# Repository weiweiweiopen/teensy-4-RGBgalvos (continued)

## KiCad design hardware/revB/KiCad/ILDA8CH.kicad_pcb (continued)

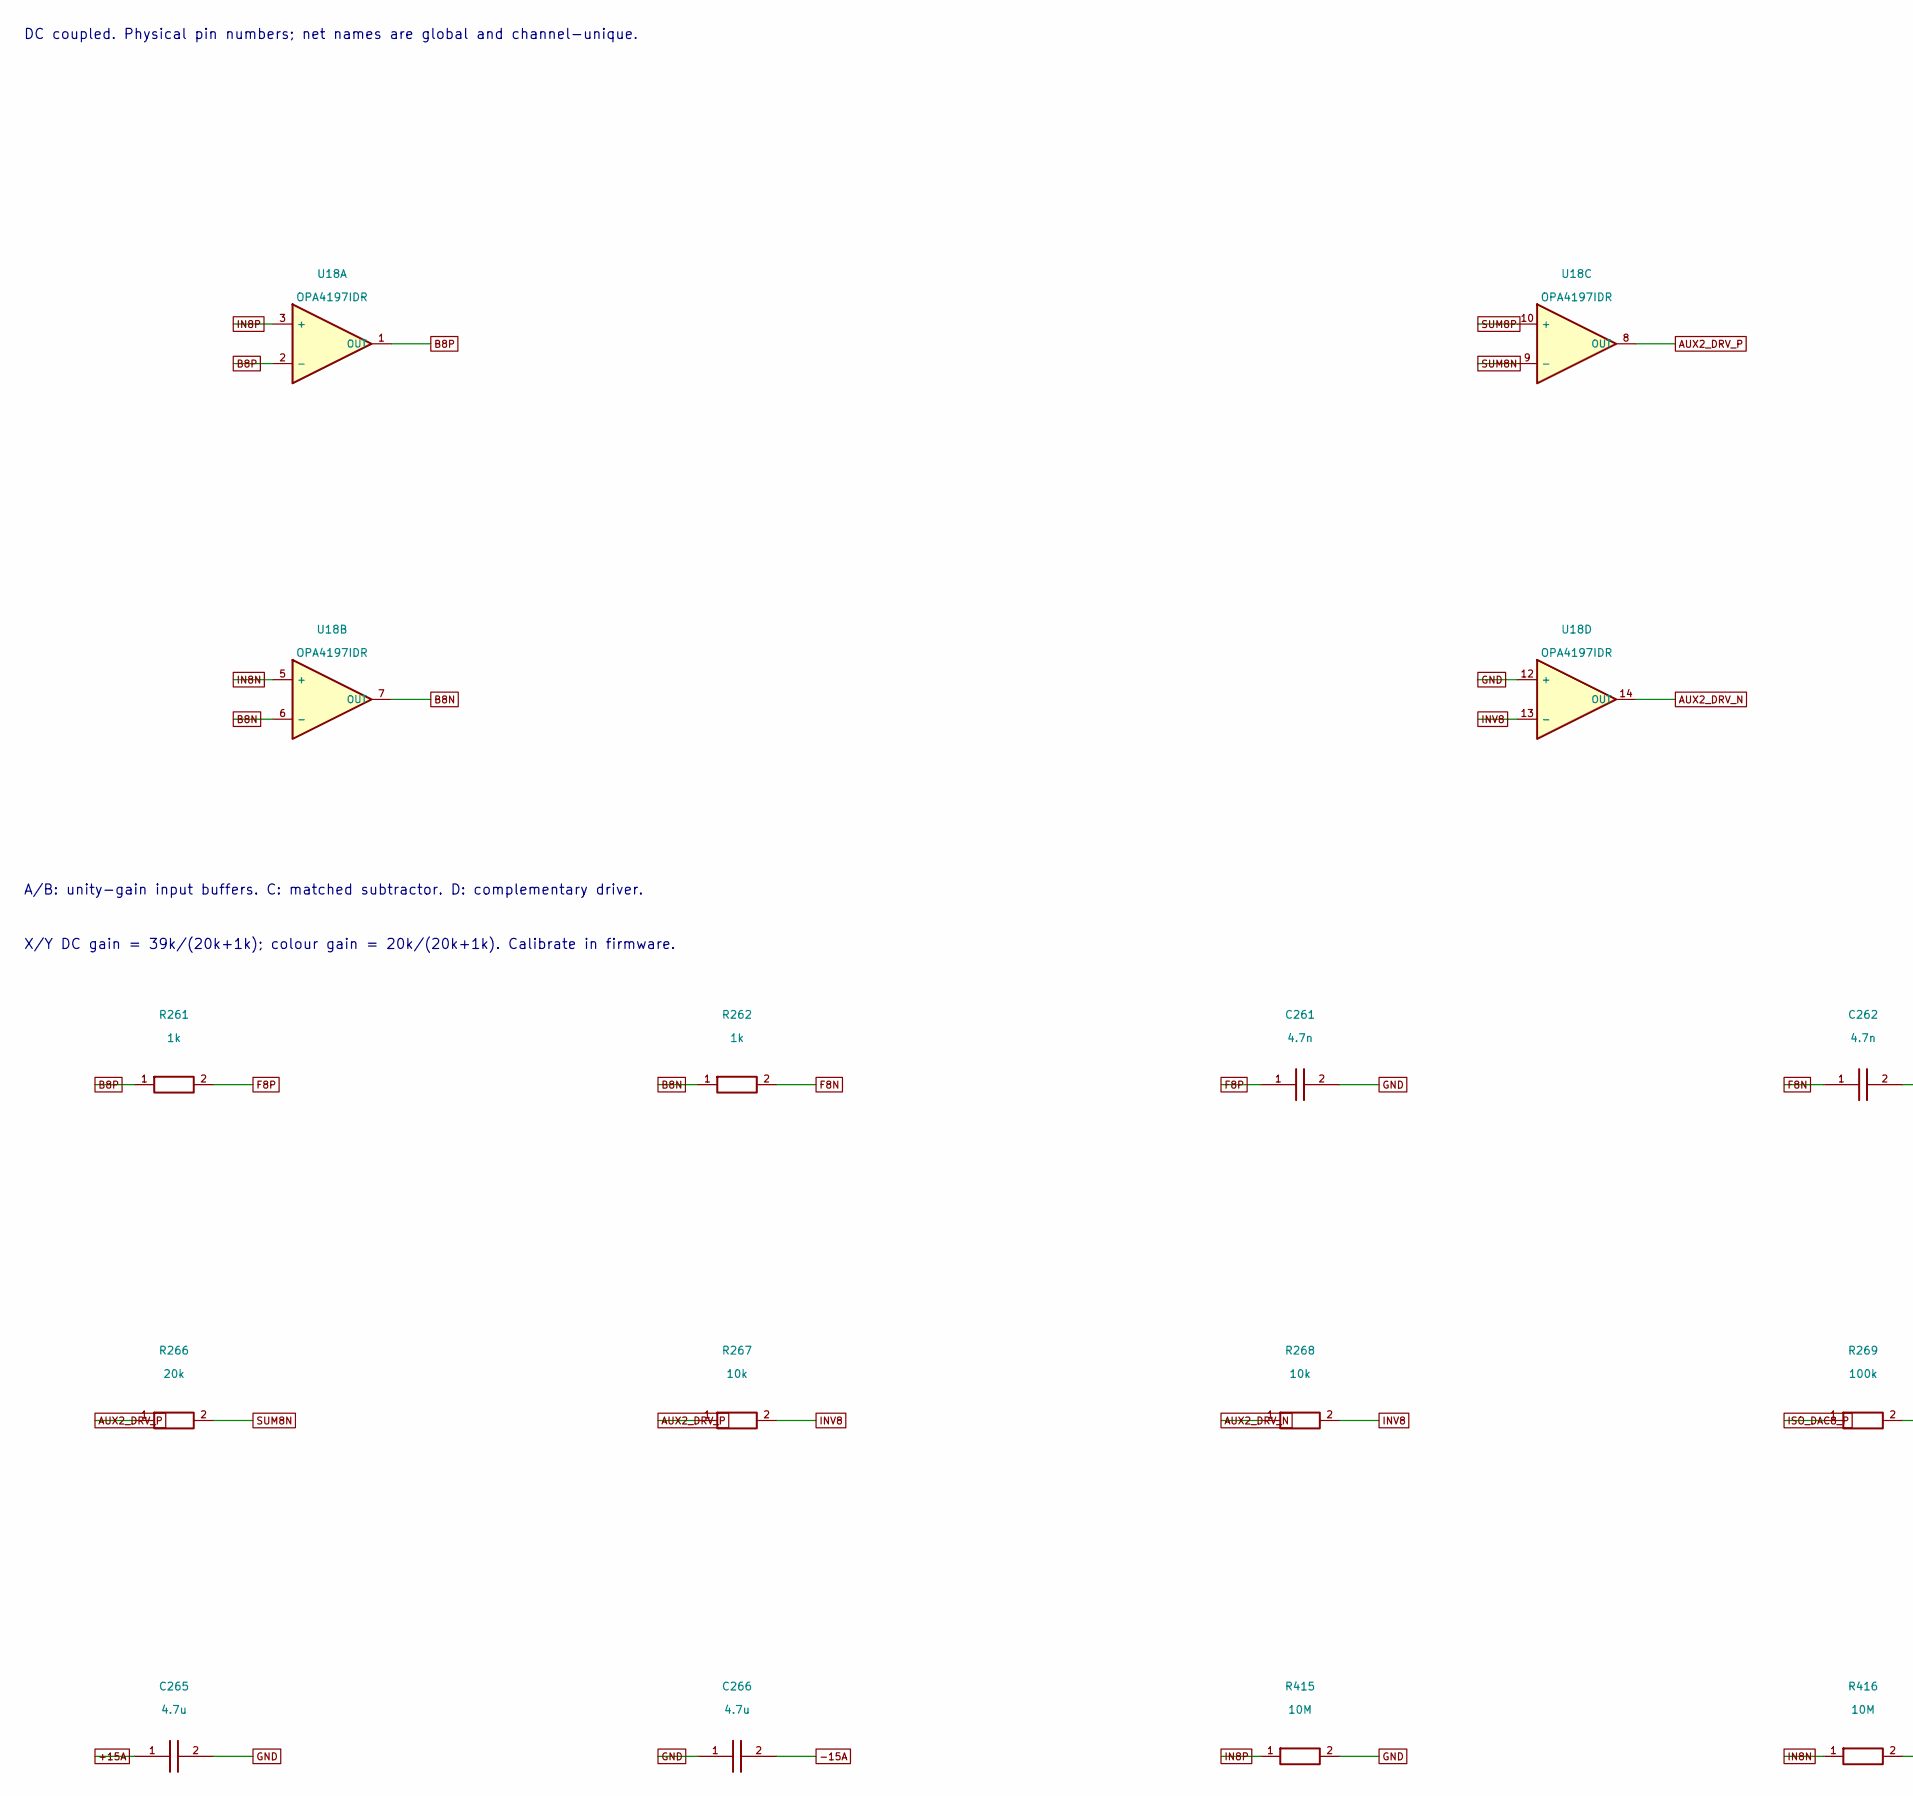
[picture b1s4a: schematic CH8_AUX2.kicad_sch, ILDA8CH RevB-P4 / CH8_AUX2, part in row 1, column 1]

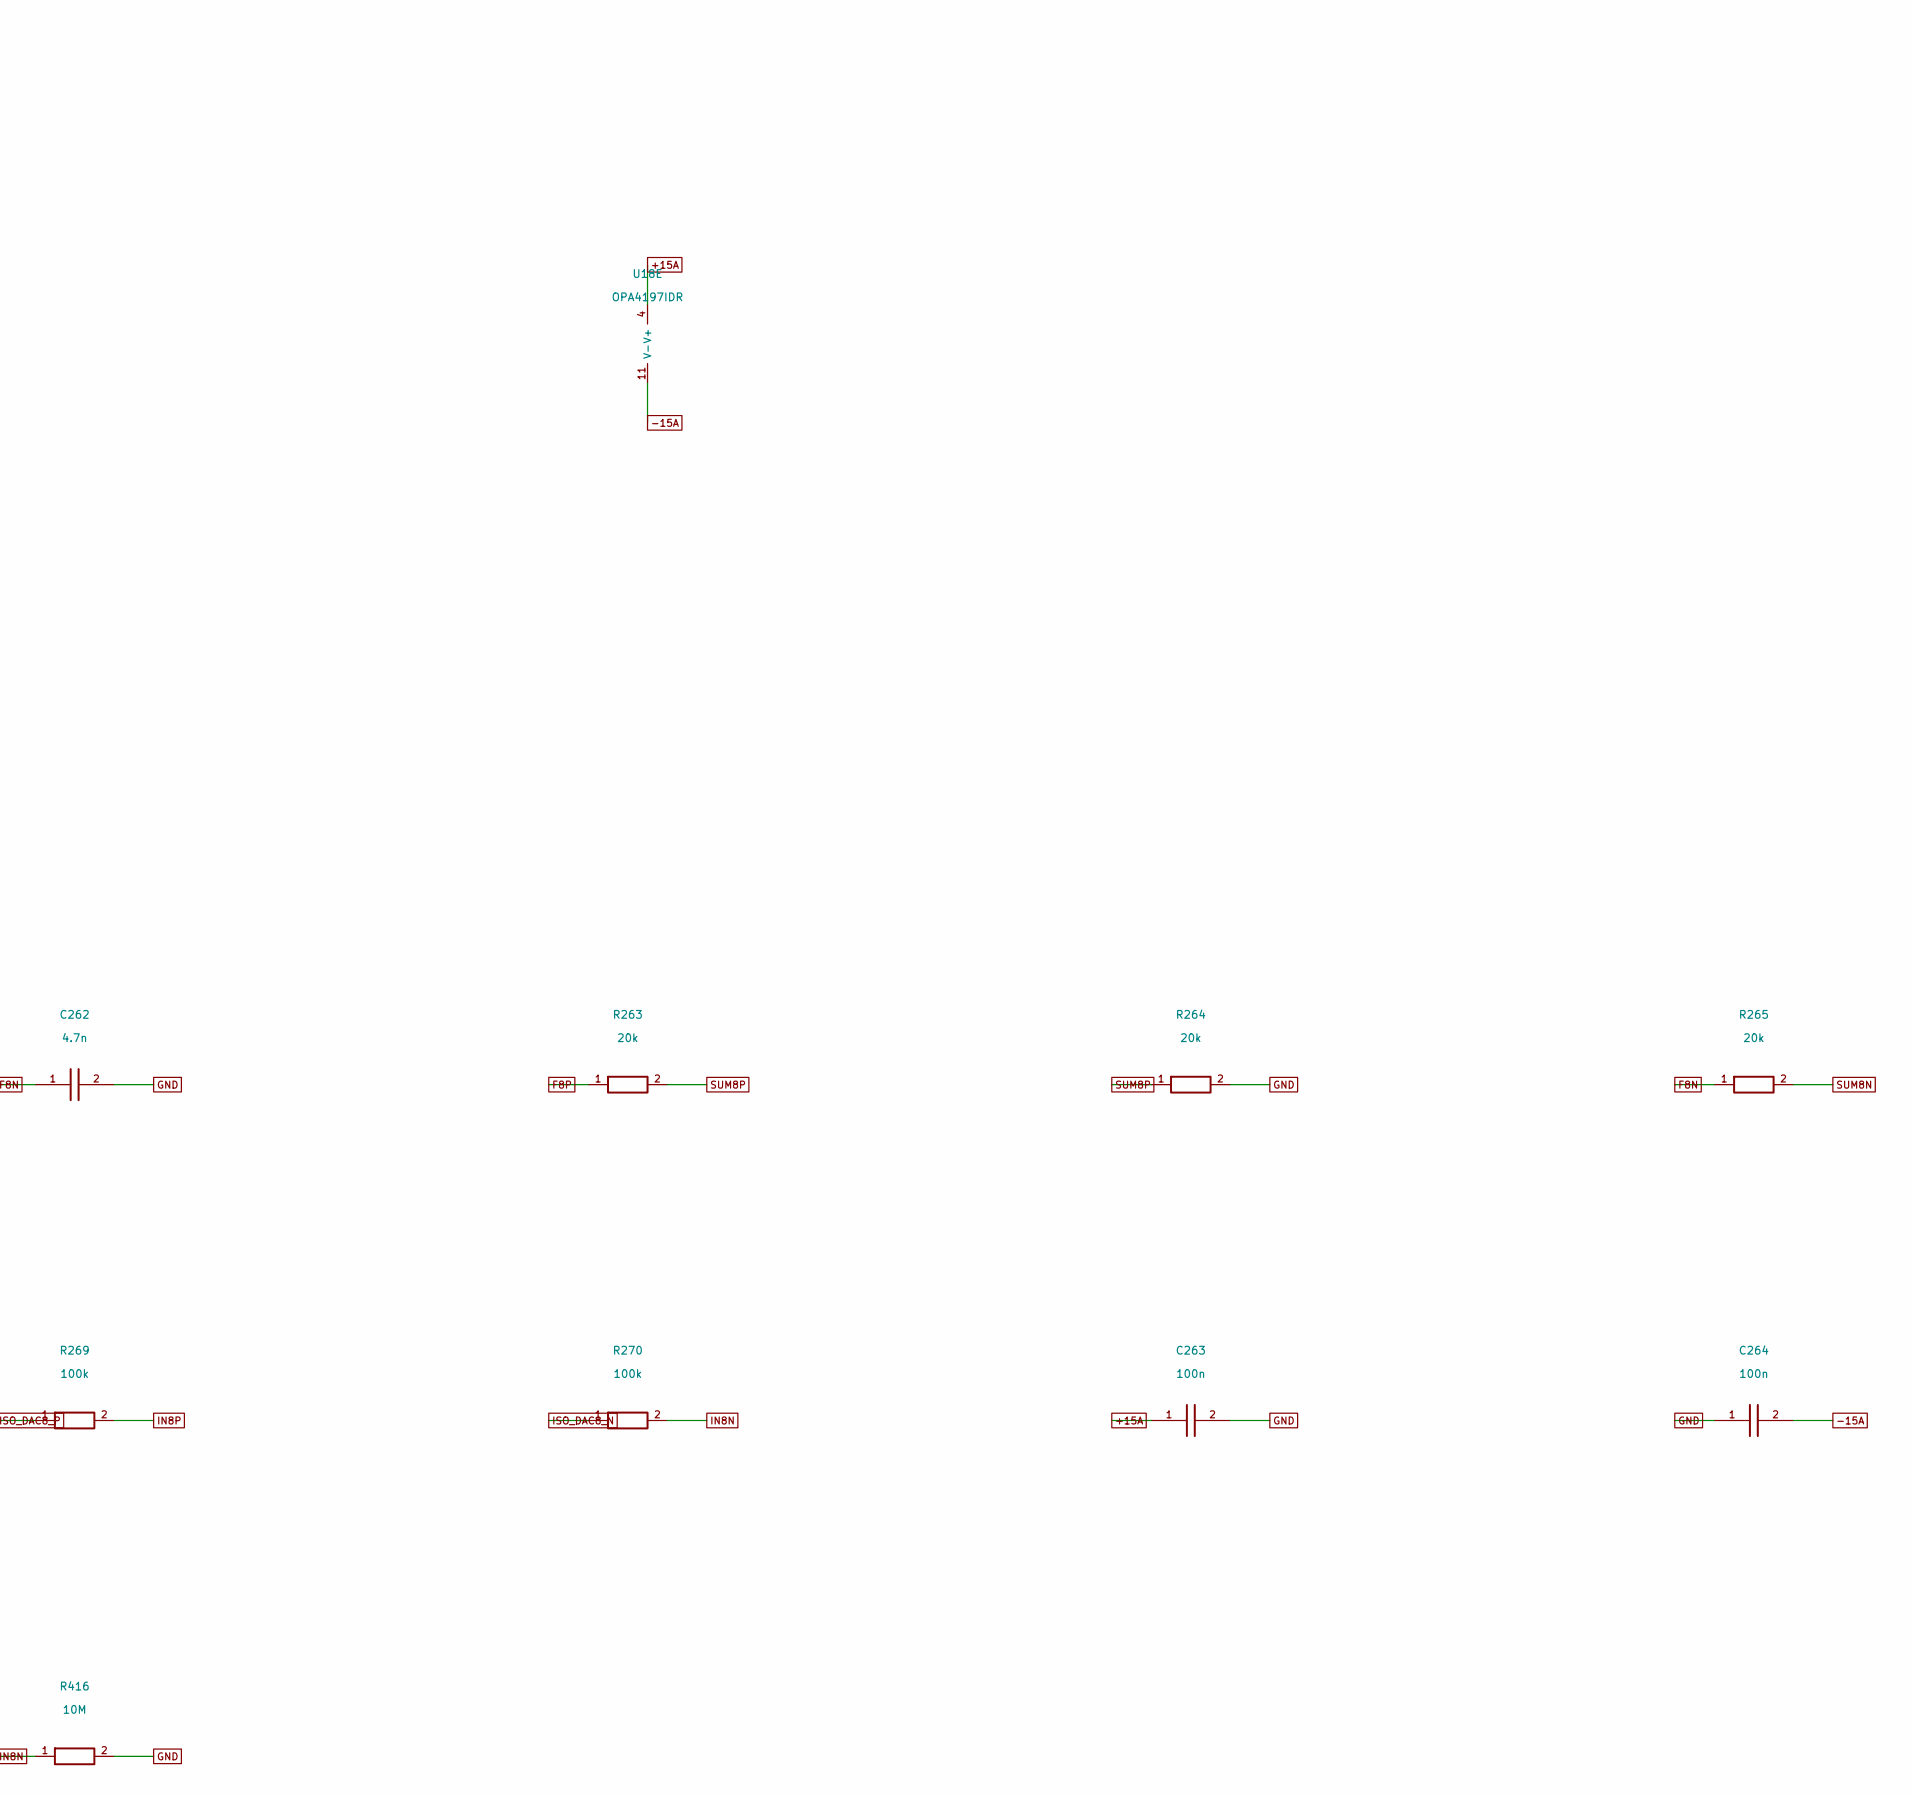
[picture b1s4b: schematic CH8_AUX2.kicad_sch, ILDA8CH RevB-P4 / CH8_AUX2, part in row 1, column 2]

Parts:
C261, C262: 4.7n; Capacitor_SMD__C_0603_1608Metric; MPN GRM1885C1H472JA01D; LCSC C85980
C263, C264: 100n; Capacitor_SMD__C_0603_1608Metric; MPN GRM188R71H104KA93D; LCSC C77055
C265, C266: 4.7u; Capacitor_SMD__C_0805_2012Metric; MPN GRM21BR61E475KA12L; LCSC C77077
R261, R262: 1k; Resistor_SMD__R_0603_1608Metric; MPN RT0603BRD071KL; LCSC C110776
R263, R264, R265, R266: 20k; Resistor_SMD__R_0603_1608Metric; MPN RT0603BRD0720KL; LCSC C723637
R267, R268: 10k; Resistor_SMD__R_0603_1608Metric; MPN RT0603BRD0710KL; LCSC C95204
R269, R270: 100k; Resistor_SMD__R_0603_1608Metric; MPN RC0603FR-07100KL; LCSC C14675
R415, R416: 10M; Resistor_SMD__R_0603_1608Metric; MPN RC0603FR-0710ML; LCSC C114606
U18: OPA4197IDR; Package_SO__SOIC-14_3.9x8.7mm_P1.27mm; MPN OPA4197IDR; LCSC C2058532

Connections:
+15A: C263.1, C265.1, U18.4 (V+); also elsewhere on the board
-15A: C264.2, C266.2, U18.11 (V-); also elsewhere on the board
AUX2_DRV_N: R268.1, U18.14 (OUT); also elsewhere on the board
AUX2_DRV_P: R266.1, R267.1, U18.8 (OUT); also elsewhere on the board
B8N: R262.1, U18.6 (-), U18.7 (OUT)
B8P: R261.1, U18.1 (OUT), U18.2 (-)
F8N: C262.1, R262.2, R265.1
F8P: C261.1, R261.2, R263.1
GND: C261.2, C262.2, C263.2, C264.1, C265.2, C266.1, R264.2, R415.2, R416.2, U18.12 (+); also elsewhere on the board
IN8N: R270.2, R416.1, U18.5 (+)
IN8P: R269.2, R415.1, U18.3 (+)
INV8: R267.2, R268.2, U18.13 (-)
ISO_DAC8_N: R270.1; also elsewhere on the board
ISO_DAC8_P: R269.1; also elsewhere on the board
SUM8N: R265.2, R266.2, U18.9 (-)
SUM8P: R263.2, R264.1, U18.10 (+)

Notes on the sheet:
DC coupled. Physical pin numbers; net names are global and channel-unique.
X/Y DC gain = 39k/(20k+1k); colour gain = 20k/(20k+1k). Calibrate in firmware.
A/B: unity-gain input buffers. C: matched subtractor. D: complementary driver.

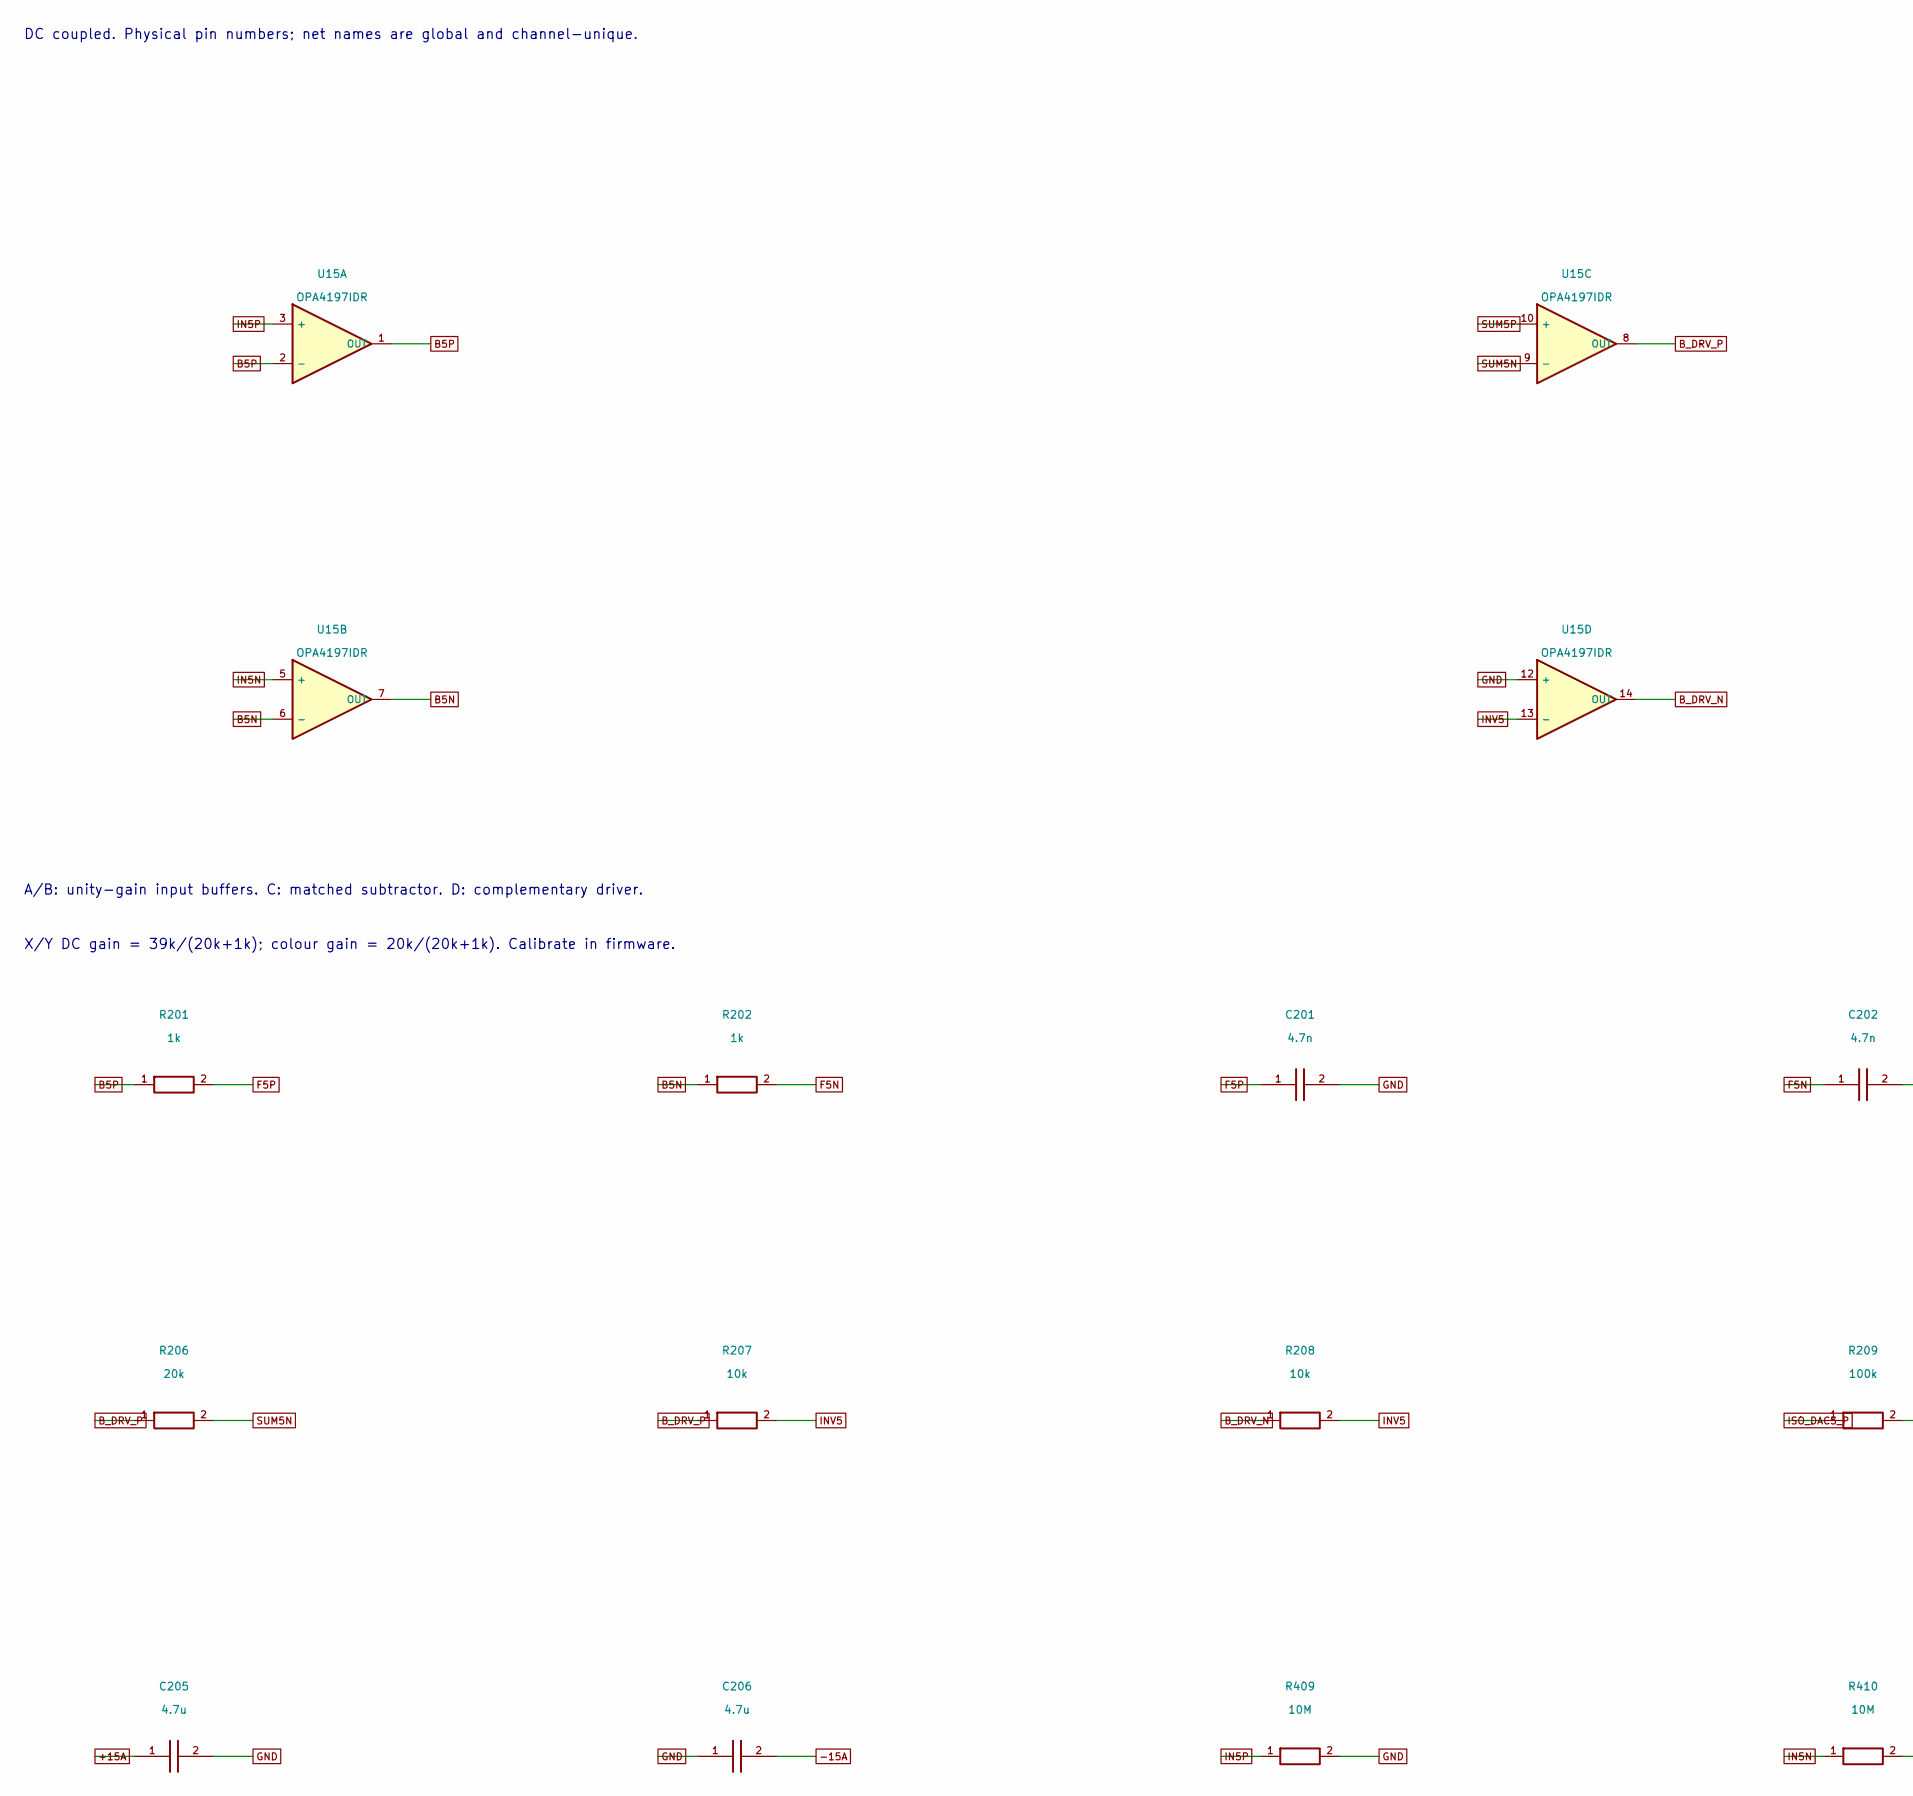
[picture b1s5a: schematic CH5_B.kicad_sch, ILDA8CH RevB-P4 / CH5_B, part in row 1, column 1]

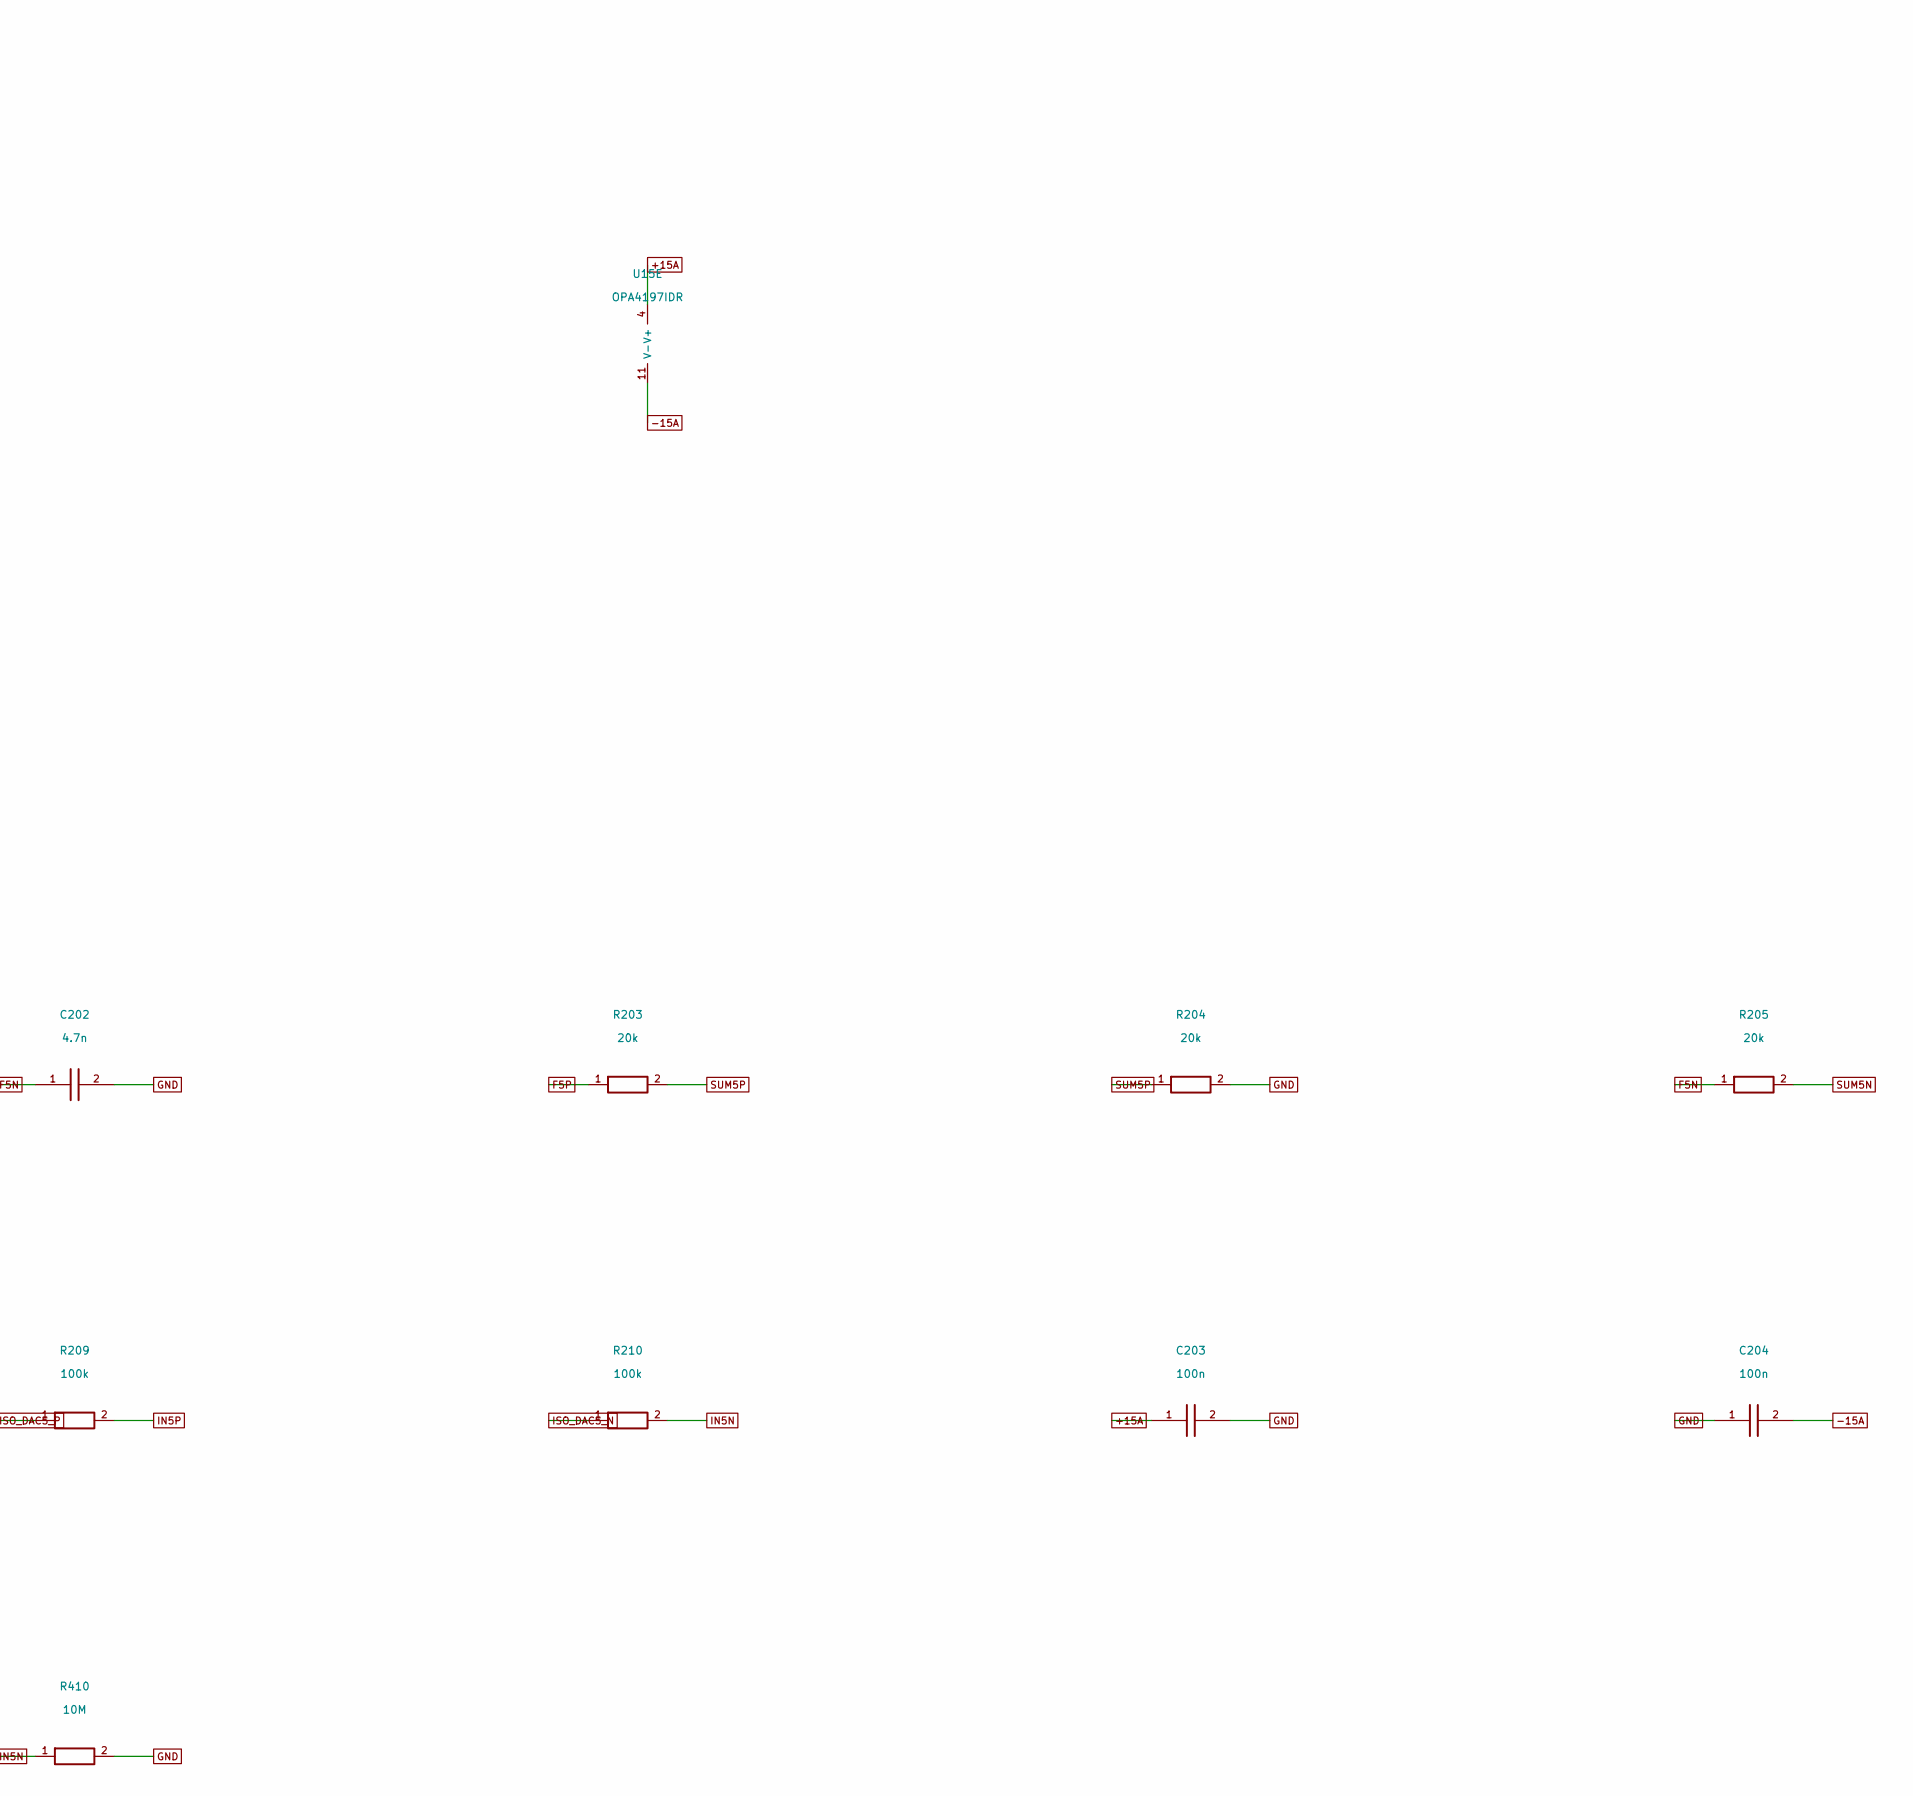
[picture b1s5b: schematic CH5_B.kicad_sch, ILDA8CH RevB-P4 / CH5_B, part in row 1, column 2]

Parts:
C201, C202: 4.7n; Capacitor_SMD__C_0603_1608Metric; MPN GRM1885C1H472JA01D; LCSC C85980
C203, C204: 100n; Capacitor_SMD__C_0603_1608Metric; MPN GRM188R71H104KA93D; LCSC C77055
C205, C206: 4.7u; Capacitor_SMD__C_0805_2012Metric; MPN GRM21BR61E475KA12L; LCSC C77077
R201, R202: 1k; Resistor_SMD__R_0603_1608Metric; MPN RT0603BRD071KL; LCSC C110776
R203, R204, R205, R206: 20k; Resistor_SMD__R_0603_1608Metric; MPN RT0603BRD0720KL; LCSC C723637
R207, R208: 10k; Resistor_SMD__R_0603_1608Metric; MPN RT0603BRD0710KL; LCSC C95204
R209, R210: 100k; Resistor_SMD__R_0603_1608Metric; MPN RC0603FR-07100KL; LCSC C14675
R409, R410: 10M; Resistor_SMD__R_0603_1608Metric; MPN RC0603FR-0710ML; LCSC C114606
U15: OPA4197IDR; Package_SO__SOIC-14_3.9x8.7mm_P1.27mm; MPN OPA4197IDR; LCSC C2058532

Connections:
+15A: C203.1, C205.1, U15.4 (V+); also elsewhere on the board
-15A: C204.2, C206.2, U15.11 (V-); also elsewhere on the board
B5N: R202.1, U15.6 (-), U15.7 (OUT)
B5P: R201.1, U15.1 (OUT), U15.2 (-)
B_DRV_N: R208.1, U15.14 (OUT); also elsewhere on the board
B_DRV_P: R206.1, R207.1, U15.8 (OUT); also elsewhere on the board
F5N: C202.1, R202.2, R205.1
F5P: C201.1, R201.2, R203.1
GND: C201.2, C202.2, C203.2, C204.1, C205.2, C206.1, R204.2, R409.2, R410.2, U15.12 (+); also elsewhere on the board
IN5N: R210.2, R410.1, U15.5 (+)
IN5P: R209.2, R409.1, U15.3 (+)
INV5: R207.2, R208.2, U15.13 (-)
ISO_DAC5_N: R210.1; also elsewhere on the board
ISO_DAC5_P: R209.1; also elsewhere on the board
SUM5N: R205.2, R206.2, U15.9 (-)
SUM5P: R203.2, R204.1, U15.10 (+)

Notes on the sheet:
DC coupled. Physical pin numbers; net names are global and channel-unique.
X/Y DC gain = 39k/(20k+1k); colour gain = 20k/(20k+1k). Calibrate in firmware.
A/B: unity-gain input buffers. C: matched subtractor. D: complementary driver.
